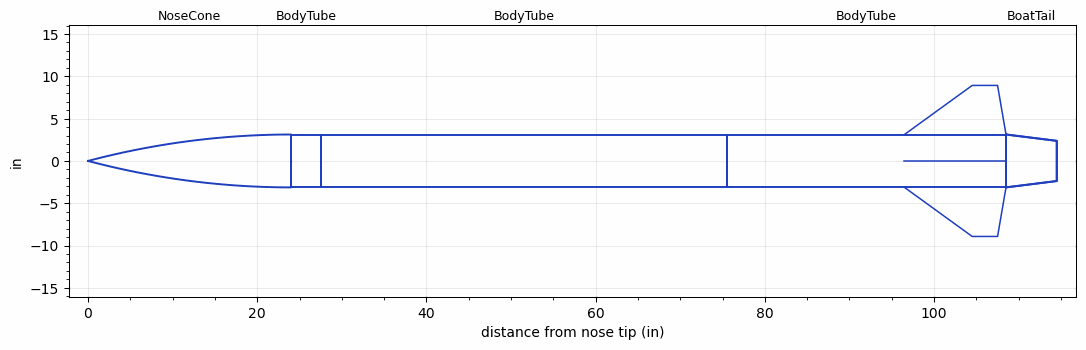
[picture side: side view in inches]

<RASAeroDocument>
 <FileVersion>2</FileVersion>
 <RocketDesign>
  <NoseCone>
   <Length>24</Length>
   <Diameter>6.25</Diameter>
   <Shape>Tangent Ogive</Shape>
   <Location>0</Location>
  </NoseCone>
  <BodyTube>
   <Length>3.5</Length>
   <Diameter>6.25</Diameter>
   <Location>24</Location>
  </BodyTube>
  <BodyTube>
   <Length>47.9999</Length>
   <Diameter>6.25</Diameter>
   <LaunchLugDiameter>0.3937</LaunchLugDiameter>
   <LaunchLugLength>0.5905</LaunchLugLength>
   <Location>27.4999</Location>
  </BodyTube>
  <BodyTube>
   <Length>32.9999</Length>
   <Diameter>6.25</Diameter>
   <LaunchLugDiameter>0.3937</LaunchLugDiameter>
   <LaunchLugLength>0.5905</LaunchLugLength>
   <Location>75.4998</Location>
   <BoattailLength>6</BoattailLength>
   <BoattailRearDiameter>4.75</BoattailRearDiameter>
   <Fin>
    <Count>4</Count>
    <Chord>12</Chord>
    <Span>5.8</Span>
    <SweepDistance>8.0017</SweepDistance>
    <TipChord>3</TipChord>
    <Thickness>0.25</Thickness>
    <Location>12</Location>
    <AirfoilSection>Rounded</AirfoilSection>
   </Fin>
  </BodyTube>
  <BoatTail>
   <Length>6</Length>
   <Diameter>6.25</Diameter>
   <RearDiameter>4.75</RearDiameter>
   <Location>108.4998</Location>
  </BoatTail>
  <Surface>Camouflage Paint</Surface>
  <ModifiedBarrowman>False</ModifiedBarrowman>
  <Turbulence>False</Turbulence>
  <UseBooster1>False</UseBooster1>
  <UseBooster2>False</UseBooster2>
 </RocketDesign>
 <LaunchSite>
  <Altitude>4995</Altitude>
  <Pressure>24.9023</Pressure>
  <RodAngle>0</RodAngle>
  <RodLength>203.9996</RodLength>
  <Temperature>41.187</Temperature>
  <WindSpeed>4.4739</WindSpeed>
 </LaunchSite>
 <Recovery>
  <Altitude1>1000</Altitude1>
  <Altitude2>0</Altitude2>
  <DeviceType1>Parachute</DeviceType1>
  <DeviceType2>None</DeviceType2>
  <Event1>True</Event1>
  <Event2>False</Event2>
  <Size1>143.9997</Size1>
  <Size2>0</Size2>
  <EventType1>Altitude</EventType1>
  <EventType2>None</EventType2>
  <CD1>0.97</CD1>
  <CD2>0</CD2>
 </Recovery>
 <SimulationList>
  <Simulation>
   <SustainerLaunchWt>72.2692</SustainerLaunchWt>
   <SustainerCG>71.0913</SustainerCG>
   <SustainerIgnitionDelay>0</SustainerIgnitionDelay>
   <Booster1SeparationDelay>0</Booster1SeparationDelay>
   <Booster1IgnitionDelay>0</Booster1IgnitionDelay>
   <IncludeBooster1>False</IncludeBooster1>
   <Booster2Delay>0</Booster2Delay>
   <IncludeBooster2>False</IncludeBooster2>
  </Simulation>
  <Simulation>
   <SustainerLaunchWt>52.8179</SustainerLaunchWt>
   <SustainerCG>60.1942</SustainerCG>
   <SustainerIgnitionDelay>0</SustainerIgnitionDelay>
   <Booster1SeparationDelay>0</Booster1SeparationDelay>
   <Booster1IgnitionDelay>0</Booster1IgnitionDelay>
   <IncludeBooster1>False</IncludeBooster1>
   <Booster2Delay>0</Booster2Delay>
   <IncludeBooster2>False</IncludeBooster2>
  </Simulation>
  <Simulation>
   <SustainerEngine>M1939W  (AT)</SustainerEngine>
   <SustainerLaunchWt>72.6335</SustainerLaunchWt>
   <SustainerCG>71.0785</SustainerCG>
   <SustainerIgnitionDelay>0</SustainerIgnitionDelay>
   <Booster1SeparationDelay>0</Booster1SeparationDelay>
   <Booster1IgnitionDelay>0</Booster1IgnitionDelay>
   <IncludeBooster1>False</IncludeBooster1>
   <Booster2Delay>0</Booster2Delay>
   <IncludeBooster2>False</IncludeBooster2>
  </Simulation>
  <Simulation>
   <SustainerLaunchWt>73.0563</SustainerLaunchWt>
   <SustainerCG>71.41</SustainerCG>
   <SustainerIgnitionDelay>0</SustainerIgnitionDelay>
   <Booster1SeparationDelay>0</Booster1SeparationDelay>
   <Booster1IgnitionDelay>0</Booster1IgnitionDelay>
   <IncludeBooster1>False</IncludeBooster1>
   <Booster2Delay>0</Booster2Delay>
   <IncludeBooster2>False</IncludeBooster2>
  </Simulation>
  <Simulation>
   <SustainerEngine>M2500T  (AT)</SustainerEngine>
   <SustainerLaunchWt>70.5959</SustainerLaunchWt>
   <SustainerCG>70.147</SustainerCG>
   <SustainerIgnitionDelay>0</SustainerIgnitionDelay>
   <Booster1SeparationDelay>0</Booster1SeparationDelay>
   <Booster1IgnitionDelay>0</Booster1IgnitionDelay>
   <IncludeBooster1>False</IncludeBooster1>
   <Booster2Delay>0</Booster2Delay>
   <IncludeBooster2>False</IncludeBooster2>
  </Simulation>
  <Simulation>
   <SustainerEngine>M1939W  (AT)</SustainerEngine>
   <SustainerLaunchWt>72.6335</SustainerLaunchWt>
   <SustainerCG>71.0785</SustainerCG>
   <SustainerIgnitionDelay>0</SustainerIgnitionDelay>
   <Booster1SeparationDelay>0</Booster1SeparationDelay>
   <Booster1IgnitionDelay>0</Booster1IgnitionDelay>
   <IncludeBooster1>False</IncludeBooster1>
   <Booster2Delay>0</Booster2Delay>
   <IncludeBooster2>False</IncludeBooster2>
  </Simulation>
 </SimulationList>
</RASAeroDocument>
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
